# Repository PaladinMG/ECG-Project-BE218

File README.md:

# ECG-Project-BE218
ECG Project files for BE218

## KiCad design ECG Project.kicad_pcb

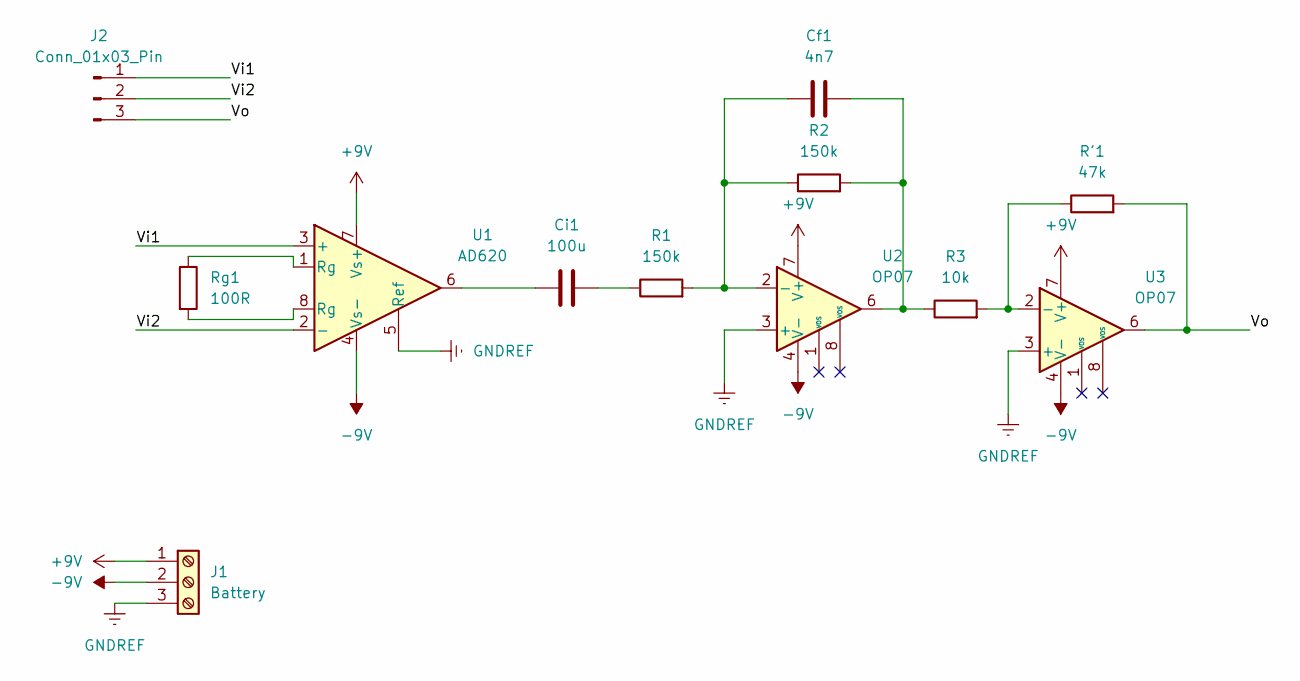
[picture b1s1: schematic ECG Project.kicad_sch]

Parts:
Cf1: 4n7; C_Disc_D4.7mm_W2.5mm_P5.00mm
Ci1: 100u; C_Radial_D8.0mm_H11.5mm_P3.50mm
J1: Battery; TerminalBlock_Phoenix_PT-1,5-3-3.5-H_1x03_P3.50mm_Horizontal
J2: Conn_01x03_Pin; PinHeader_1x03_P2.54mm_Vertical
R1, R2: 150k; R_Axial_DIN0207_L6.3mm_D2.5mm_P10.16mm_Horizontal
R3: 10k; R_Axial_DIN0207_L6.3mm_D2.5mm_P10.16mm_Horizontal
R'1: 47k; R_Axial_DIN0207_L6.3mm_D2.5mm_P10.16mm_Horizontal
Rg1: 100R; R_Axial_DIN0207_L6.3mm_D2.5mm_P10.16mm_Horizontal
U1: AD620; DIP-8_W7.62mm
U2, U3: OP07; DIP-8_W7.62mm

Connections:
+9V: J1.1, U1.7 (Vs+), U2.7 (V+), U3.7 (V+)
-9V: J1.2, U1.4 (Vs-), U2.4 (V-), U3.4 (V-)
/Vi1: J2.1, U1.3 (+)
/Vi2: J2.2, U1.2 (-)
/Vo: J2.3, R'1.2, U3.6
GNDREF: J1.3, U1.5 (Ref), U2.3 (+), U3.3 (+)
unnamed: Cf1.2, R2.2, R3.1, U2.6
unnamed: Ci1.1, U1.6
unnamed: Ci1.2, R1.1
unnamed: Rg1.1, U1.1 (Rg)
unnamed: Rg1.2, U1.8 (Rg)
unnamed: Cf1.1, R1.2, R2.1, U2.2 (-)
unnamed: R3.2, R'1.1, U3.2 (-)

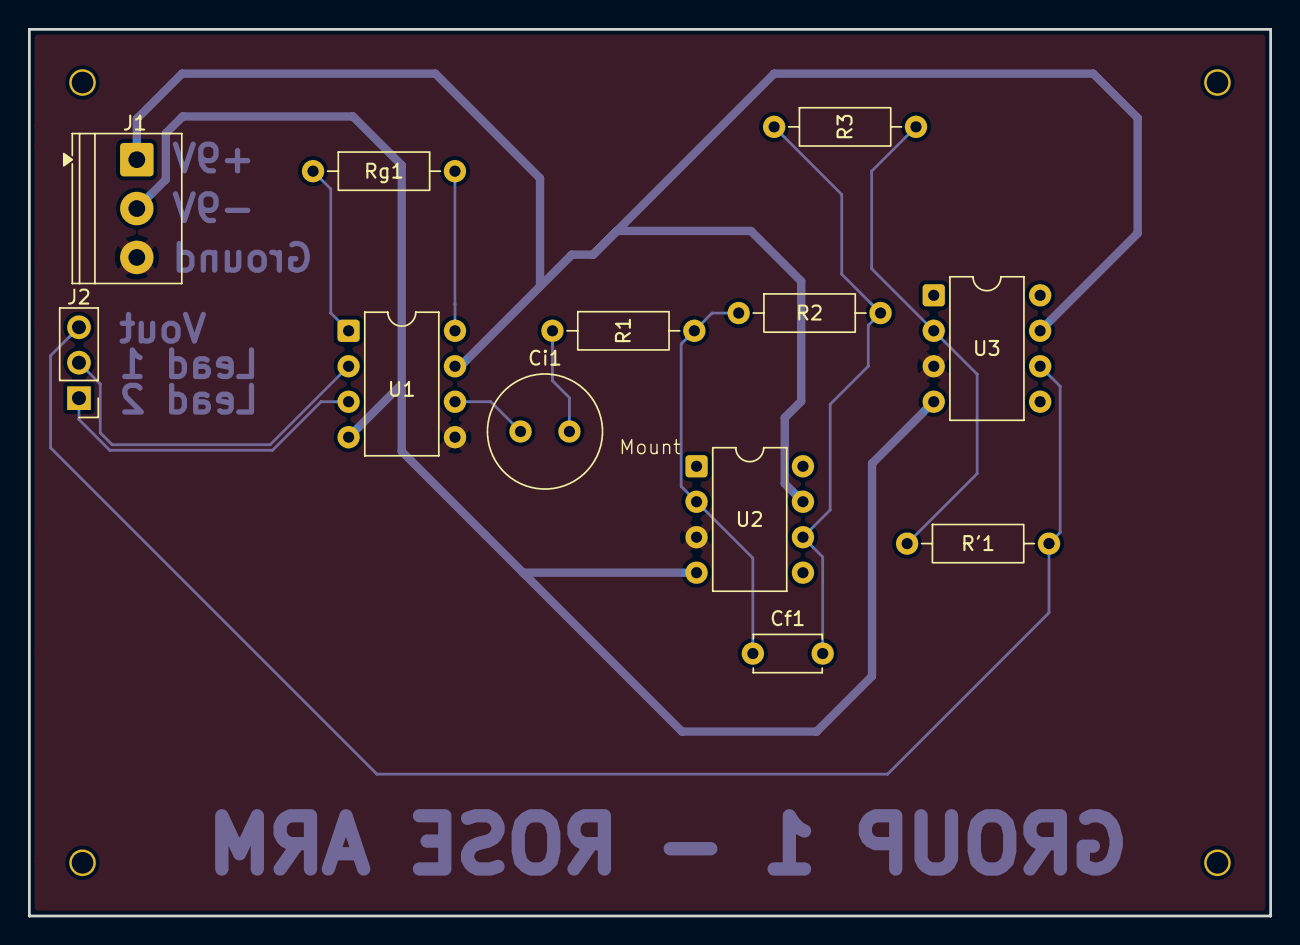
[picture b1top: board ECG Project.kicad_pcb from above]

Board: 2 copper layers, 88.9 x 63.5 mm, 13 parts (0 on the bottom side), 13 nets.

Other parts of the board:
Mount: Mounting Holes; Untitled
